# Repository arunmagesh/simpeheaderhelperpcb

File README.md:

# simpeheaderhelperpcb
repo for the simple header helper pcb

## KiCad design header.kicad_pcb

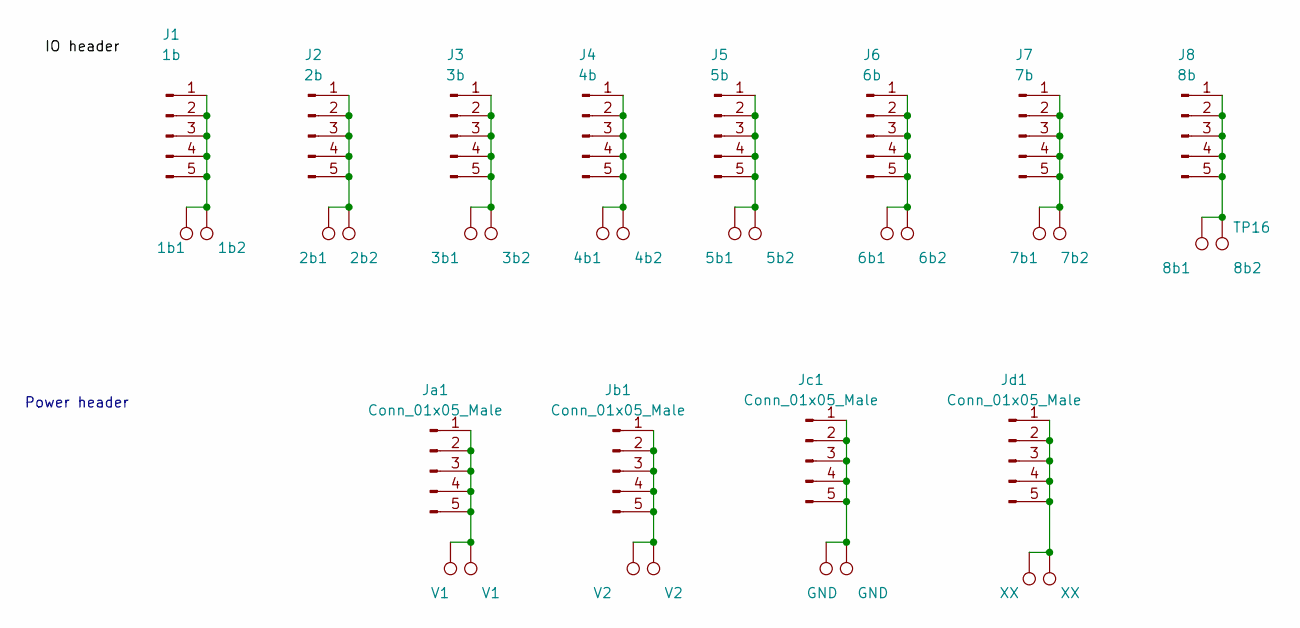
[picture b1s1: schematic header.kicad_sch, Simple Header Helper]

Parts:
J1: 1b; PinHeader_1x05_P2.54mm_Vertical
J2: 2b; PinHeader_1x05_P2.54mm_Vertical
J3: 3b; PinHeader_1x05_P2.54mm_Vertical
J4: 4b; PinHeader_1x05_P2.54mm_Vertical
J5: 5b; PinHeader_1x05_P2.54mm_Vertical
J6: 6b; PinHeader_1x05_P2.54mm_Vertical
J7: 7b; PinHeader_1x05_P2.54mm_Vertical
J8: 8b; PinHeader_1x05_P2.54mm_Vertical
Ja1: Conn_01x05_Male; PinHeader_1x05_P2.54mm_Vertical
Jb1: Conn_01x05_Male; PinHeader_1x05_P2.54mm_Vertical
Jc1: Conn_01x05_Male; PinHeader_1x05_P2.54mm_Vertical
Jd1: Conn_01x05_Male; PinHeader_1x05_P2.54mm_Vertical
TP1: 1b1; TestPoint_Pad_4.0x4.0mm
TP2: 1b2; TestPoint_Pad_4.0x4.0mm
TP3: 2b1; TestPoint_Pad_4.0x4.0mm
TP4: 2b2; TestPoint_Pad_4.0x4.0mm
TP5: 3b1; TestPoint_Pad_4.0x4.0mm
TP6: 3b2; TestPoint_Pad_4.0x4.0mm
TP7: 4b1; TestPoint_Pad_4.0x4.0mm
TP8: 4b2; TestPoint_Pad_4.0x4.0mm
TP9: 5b1; TestPoint_Pad_4.0x4.0mm
TP10: 5b2; TestPoint_Pad_4.0x4.0mm
TP11: 6b1; TestPoint_Pad_4.0x4.0mm
TP12: 6b2; TestPoint_Pad_4.0x4.0mm
TP13: 7b1; TestPoint_Pad_4.0x4.0mm
TP14: 7b2; TestPoint_Pad_4.0x4.0mm
TP15: 8b1; TestPoint_Pad_4.0x4.0mm
TP16: 8b2; TestPoint_Pad_4.0x4.0mm
TP17, TP18: V1; TestPoint_Pad_4.0x4.0mm
TP19, TP20: V2; TestPoint_Pad_4.0x4.0mm
TP21, TP22: GND; TestPoint_Pad_4.0x4.0mm
TP23, TP24: XX; TestPoint_Pad_4.0x4.0mm

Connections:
unnamed: J1.1, J1.2, J1.3, J1.4, J1.5, TP1.1, TP2.1
unnamed: J2.1, J2.2, J2.3, J2.4, J2.5, TP3.1, TP4.1
unnamed: J3.1, J3.2, J3.3, J3.4, J3.5, TP5.1, TP6.1
unnamed: J4.1, J4.2, J4.3, J4.4, J4.5, TP7.1, TP8.1
unnamed: J5.1, J5.2, J5.3, J5.4, J5.5, TP9.1, TP10.1
unnamed: J6.1, J6.2, J6.3, J6.4, J6.5, TP11.1, TP12.1
unnamed: J7.1, J7.2, J7.3, J7.4, J7.5, TP13.1, TP14.1
unnamed: J8.1, J8.2, J8.3, J8.4, J8.5, TP15.1, TP16.1
unnamed: Ja1.1, Ja1.2, Ja1.3, Ja1.4, Ja1.5, TP17.1, TP18.1
unnamed: Jb1.1, Jb1.2, Jb1.3, Jb1.4, Jb1.5, TP19.1, TP20.1
unnamed: Jc1.1, Jc1.2, Jc1.3, Jc1.4, Jc1.5, TP21.1, TP22.1
unnamed: Jd1.1, Jd1.2, Jd1.3, Jd1.4, Jd1.5, TP23.1, TP24.1

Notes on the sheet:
Power header

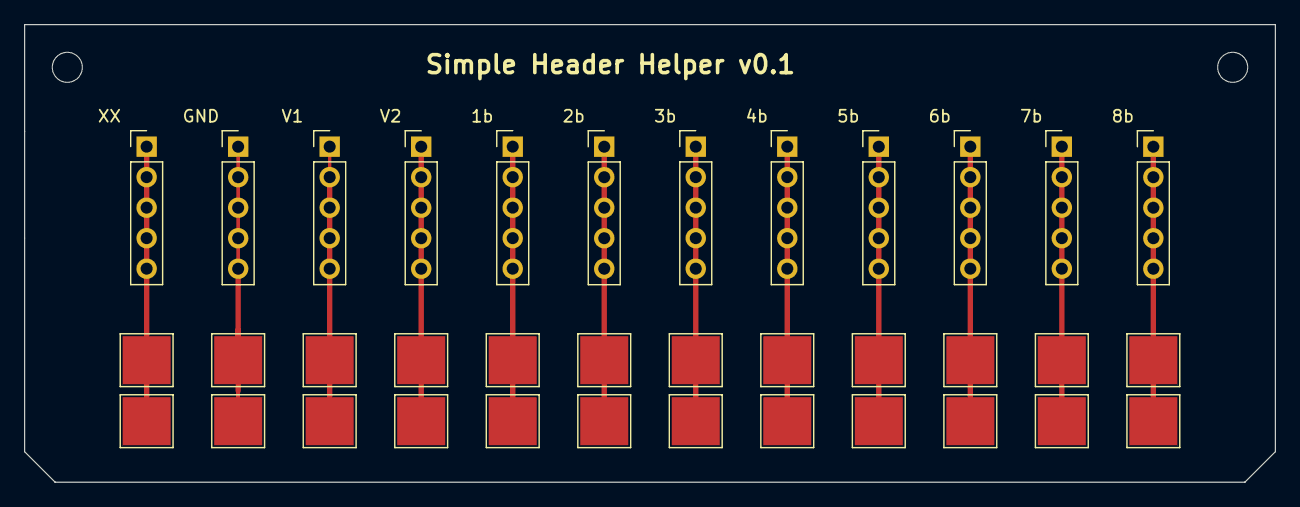
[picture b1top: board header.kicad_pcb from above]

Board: 2 copper layers, 104.1 x 38.1 mm, 37 parts (0 on the bottom side), 12 nets.

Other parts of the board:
REF1: MountingHole_2.5mm
